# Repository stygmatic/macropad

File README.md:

Meddys macropad

This macropad is a 4 key macropad with an OLED Display
I will use it on my pc to control my spotify and mic settings as well as display music info. It also has 4 neopixels which will light up every time i press a key.

Features:
It will be printed in a translucent green filament like my rocket
128x32 OLED Display
4 Keys
4 neopixels

The case is 1 piece and the pcb should be able to slide into the case and still be screwed in nicely

Schematic

My case, made in OnShape

PCB
My pcb was made in kicad, which ive been using for everything :D

I used MX_V2 for the keyswitch footprints. I think in retrospect, I should've added a ground plane

Firmware Overview
This hackpad uses QMK firmware.

The macropad has 4 keys which will be used as my push to talk key, and then the next, previous, and pause/resume for my spotify.
The oled will display the current song playing(still have to figure out the firmware for that)

BOM:

4x Blue MX Switches(I already have)

4x Keycaps

3x 3.2mm screws

2X 3.2mm Bolts

4X capacitors.
https://www.amazon.com/mxuteuk-Multilayer-Monolithic-Capacitor-0-1uf-104/dp/B08B3VCK42/

4X Neopixels

1x 0.96" OLED Display

1x XIAO RP2040

1x Case

I like rockets

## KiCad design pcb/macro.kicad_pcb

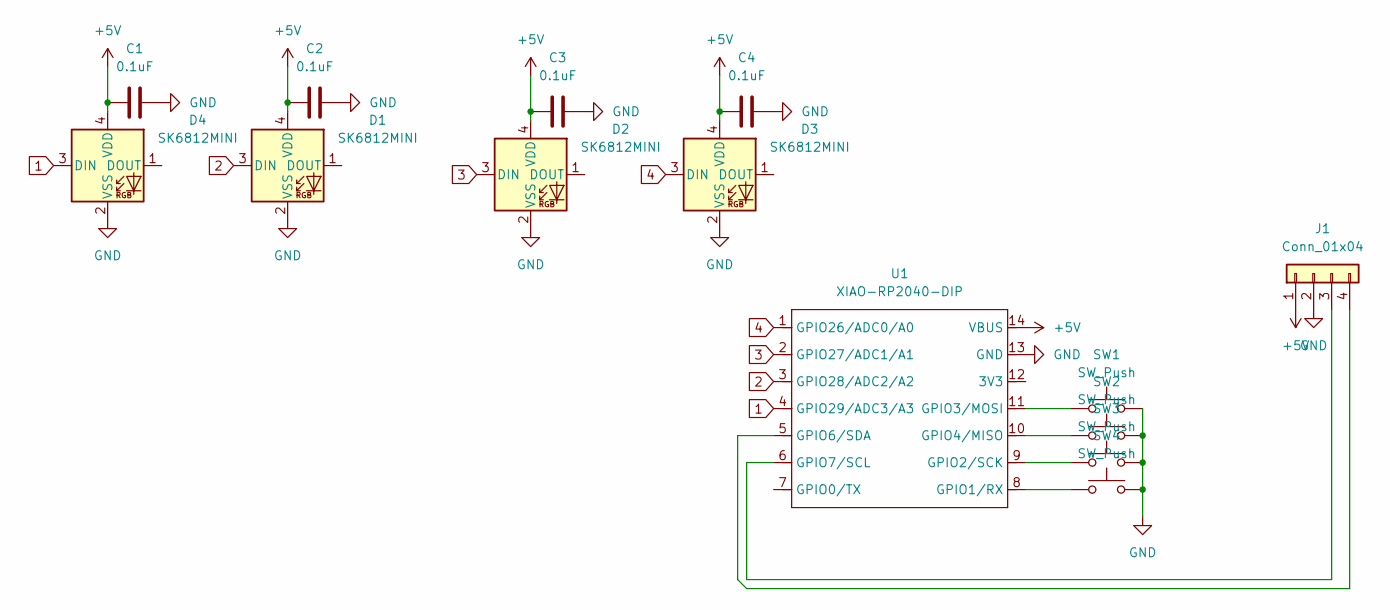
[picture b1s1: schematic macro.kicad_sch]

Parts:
C1, C2, C3, C4: 0.1uF; C_Axial_L3.8mm_D2.6mm_P7.50mm_Horizontal
D1, D2, D3, D4: SK6812MINI; LED_SK6812MINI_PLCC4_3.5x3.5mm_P1.75mm
J1: Conn_01x04; PinSocket_1x04_P2.54mm_Vertical
SW1, SW2, SW3, SW4: SW_Push; SW_Cherry_MX_1.00u_PCB
U1: XIAO-RP2040-DIP

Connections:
1: D4.3 (DIN), U1.4 (GPIO29/ADC3/A3)
2: D1.3 (DIN), U1.3 (GPIO28/ADC2/A2)
3: D2.3 (DIN), U1.2 (GPIO27/ADC1/A1)
4: D3.3 (DIN), U1.1 (GPIO26/ADC0/A0)
+5V: C1.1, C2.1, C3.1, C4.1, D1.4 (VDD), D2.4 (VDD), D3.4 (VDD), D4.4 (VDD), J1.1, U1.14 (VBUS)
GND: C1.2, C2.2, C3.2, C4.2, D1.2 (VSS), D2.2 (VSS), D3.2 (VSS), D4.2 (VSS), J1.2, SW1.2, SW2.2, SW3.2, SW4.2, U1.13 (GND)
unnamed: J1.3, U1.6 (GPIO7/SCL)
unnamed: J1.4, U1.5 (GPIO6/SDA)
unnamed: SW4.1, U1.8 (GPIO1/RX)
unnamed: SW3.1, U1.9 (GPIO2/SCK)
unnamed: SW1.1, U1.11 (GPIO3/MOSI)
unnamed: SW2.1, U1.10 (GPIO4/MISO)

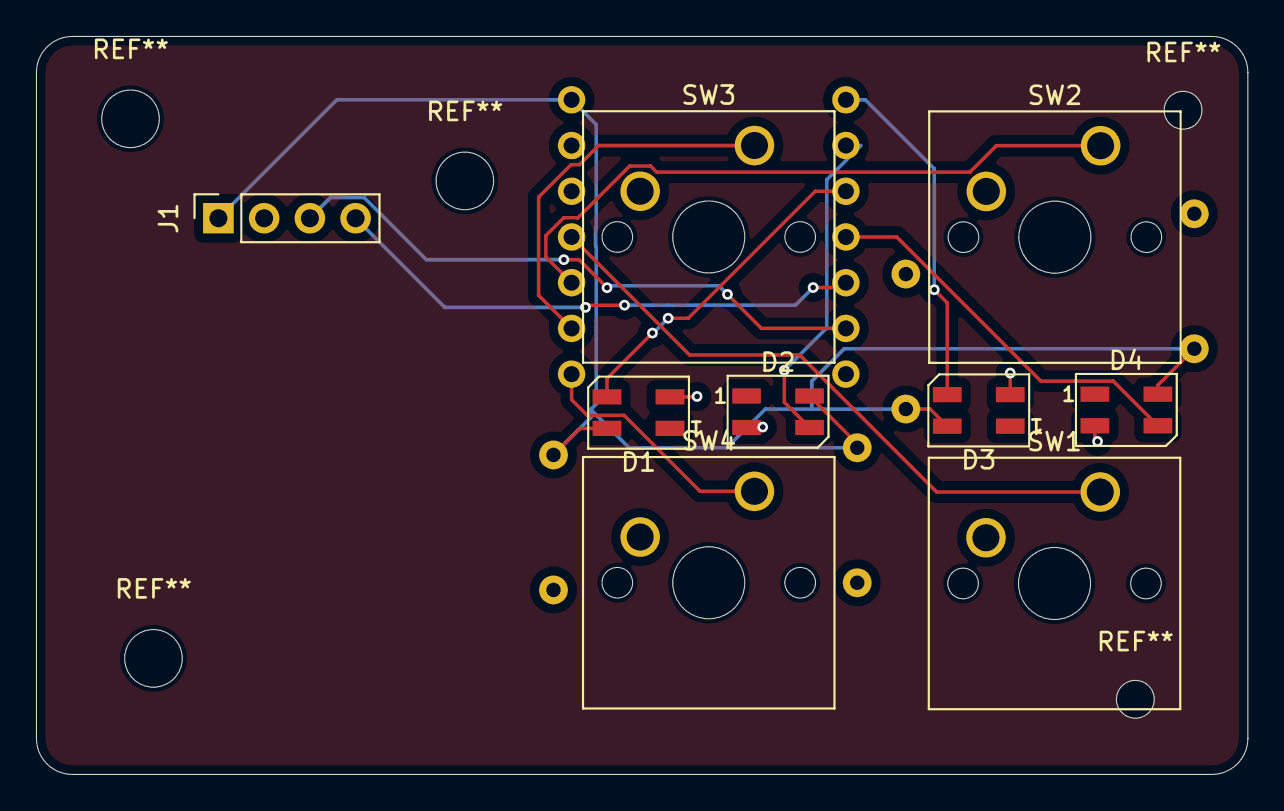
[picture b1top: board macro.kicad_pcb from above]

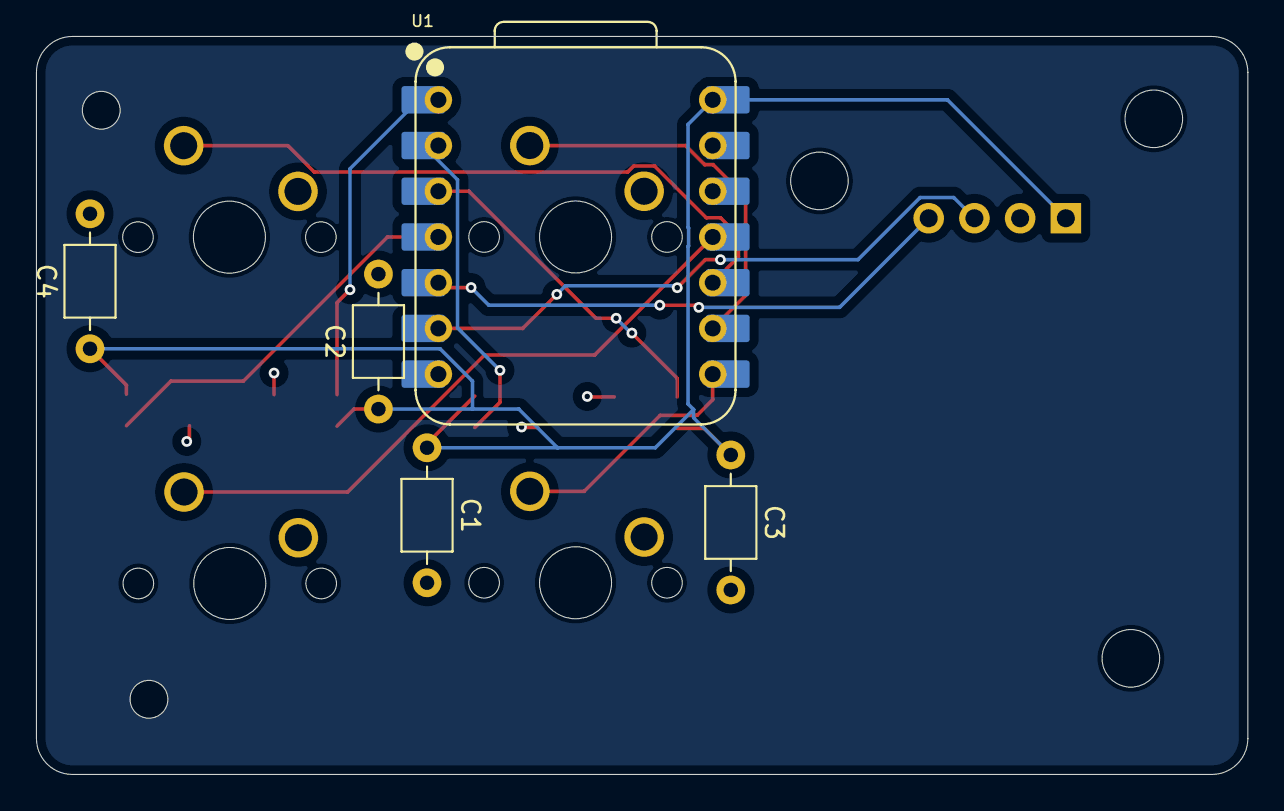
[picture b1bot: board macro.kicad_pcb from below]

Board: 4 copper layers, 67.3 x 41.0 mm, 14 parts (5 on the bottom side), 12 nets.
